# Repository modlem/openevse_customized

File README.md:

# openevse_customized
My own modified OpenEVSE

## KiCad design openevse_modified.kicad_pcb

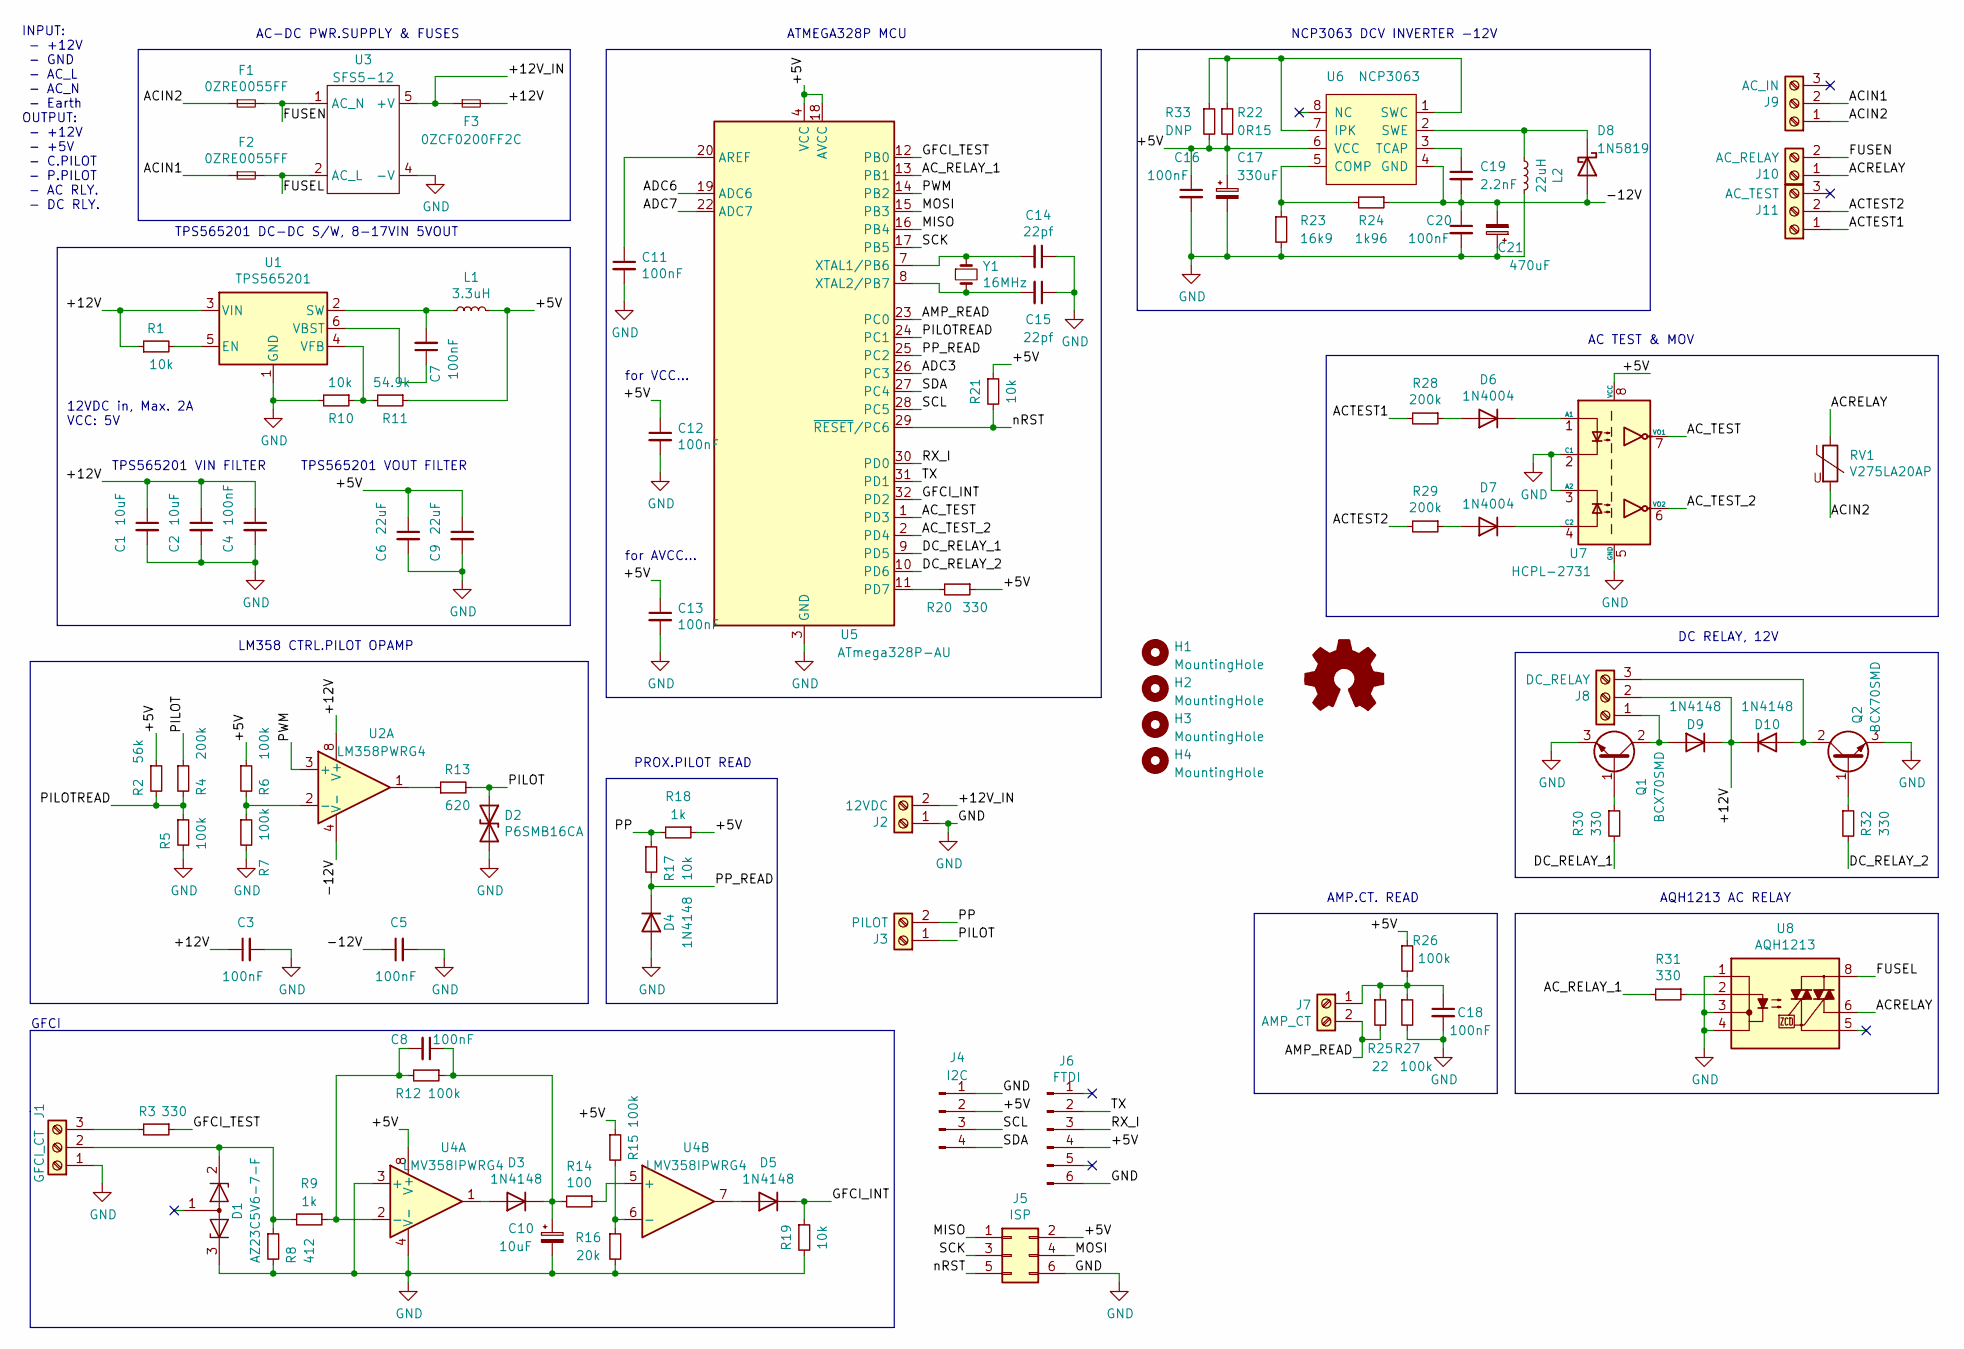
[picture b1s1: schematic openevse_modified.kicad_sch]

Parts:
C1, C2: 10uF; C_1210_3225Metric_Pad1.33x2.70mm_HandSolder
C3, C4, C5, C7, C8, C11, C12, C13, C16, C18, C20: 100nF; C_0805_2012Metric_Pad1.18x1.45mm_HandSolder
C6, C9: 22uF; C_0805_2012Metric_Pad1.18x1.45mm_HandSolder
C10: 10uF; CP_EIA-3216-18_Kemet-A_Pad1.58x1.35mm_HandSolder
C14, C15: 22pf; C_0805_2012Metric_Pad1.18x1.45mm_HandSolder
C17: 330uF; CP_Elec_8x10
C19: 2.2nF; C_0805_2012Metric_Pad1.18x1.45mm_HandSolder
C21: 470uF; CP_Radial_D12.5mm_P5.00mm
D1: AZ23C5V6-7-F; SOT-23
D2: P6SMB16CA; D_SMB_Handsoldering
D3, D4, D5, D9, D10: 1N4148; D_DO-35_SOD27_P7.62mm_Horizontal
D6, D7: 1N4004; D_DO-41_SOD81_P10.16mm_Horizontal
D8: 1N5819; D_SOD-123
F1, F2: 0ZRE0055FF; Fuse_BelFuse_0ZRE0055FF_L14.0mm_W4.1mm
F3: 0ZCF0200FF2C; Fuse_2920_7451Metric_Pad2.10x5.45mm_HandSolder
H1, H2, H3, H4: MountingHole; MountingHole_3.5mm
J1: GFCI_CT; JST_XH_B3B-XH-AM_1x03_P2.50mm_Vertical
J2: 12VDC; MC002075
J3: PILOT; MC002075
J4: I2C; JST_XH_B4B-XH-AM_1x04_P2.50mm_Vertical
J5: ISP; PinHeader_2x03_P2.54mm_Vertical
J6: FTDI; JST_XH_B6B-XH-AM_1x06_P2.50mm_Vertical
J7: AMP_CT; JST_XH_B2B-XH-AM_1x02_P2.50mm_Vertical
J8: DC_RELAY; MC002076
J9: AC_IN; MC002076
J10: AC_RELAY; MC002075
J11: AC_TEST; MC002076
L1: 3.3uH; L_TDK_VLP8040
L2: 22uH; L_Bourns_SRN6045TA
Q1, Q2: BCX70SMD; SOT-23_Handsoldering
R1, R10, R17, R19, R21: 10k; R_0805_2012Metric_Pad1.20x1.40mm_HandSolder
R2: 56k; R_0805_2012Metric_Pad1.20x1.40mm_HandSolder
R3, R20, R30, R31, R32: 330; R_0805_2012Metric_Pad1.20x1.40mm_HandSolder
R4: 200k; R_0805_2012Metric_Pad1.20x1.40mm_HandSolder
R5, R6, R7, R12, R15, R26, R27: 100k; R_0805_2012Metric_Pad1.20x1.40mm_HandSolder
R8: 412; R_0805_2012Metric_Pad1.20x1.40mm_HandSolder
R9, R18: 1k; R_0805_2012Metric_Pad1.20x1.40mm_HandSolder
R11: 54.9k; R_0805_2012Metric_Pad1.20x1.40mm_HandSolder
R13: 620; R_0805_2012Metric_Pad1.20x1.40mm_HandSolder
R14: 100; R_0805_2012Metric_Pad1.20x1.40mm_HandSolder
R16: 20k; R_0805_2012Metric_Pad1.20x1.40mm_HandSolder
R22: 0R15; R_0805_2012Metric_Pad1.20x1.40mm_HandSolder
R23: 16k9; R_0805_2012Metric_Pad1.20x1.40mm_HandSolder
R24: 1k96; R_0805_2012Metric_Pad1.20x1.40mm_HandSolder
R25: 22; R_0805_2012Metric_Pad1.20x1.40mm_HandSolder
R28, R29: 200k; R_Axial_DIN0207_L6.3mm_D2.5mm_P10.16mm_Horizontal
R33: DNP; R_1210_3225Metric_Pad1.30x2.65mm_HandSolder
RV1: V275LA20AP; RV_Disc_D15.5mm_W3.9mm_P7.5mm
U1: TPS565201; SOT-23-6
U2: LM358PWRG4; TSSOP-8_4.4x3mm_P0.65mm
U3: SFS5-12; Converter_ACDC_Recom_RAC20-xxDK_THT
U4: LMV358IPWRG4; TSSOP-8_4.4x3mm_P0.65mm
U5: ATmega328P-AU; TQFP-32_7x7mm_P0.8mm
U6: NCP3063; SOIC-8-1EP_3.9x4.9mm_P1.27mm_EP2.29x3mm
U7: HCPL-2731; DIP-8_W7.62mm_LongPads
U8: AQH1213; DIP-8_W7.62mm_LongPads
Y1: 16MHz; Crystal_SMD_HC49-SD_HandSoldering

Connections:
/+5V: C6.1, C9.1, C12.1, C13.1, C16.1, C17.1, J4.2, J5.2, J6.4, L1.2, R2.1, R6.1, R11.1, R15.1, R18.1, R20.1, R21.1, R22.2, R26.1, R33.2, U4.8 (V+), U5.4 (VCC), U5.6 (VCC), U5.18 (AVCC), U6.6 (VCC), U7.8 (VCC)
/+12V: C1.1, C2.1, C3.1, C4.1, D9.1 (K), D10.1 (K), F3.2, J8.2, R1.1, U1.3 (VIN), U2.8 (V+); also elsewhere on the board
/+12V_IN: F3.1, J2.2, U3.5 (+V); also elsewhere on the board
/-12V: C5.1, C19.2, C20.1, C21.2, D8.2 (A), R24.1, U2.4 (V-), U6.4 (GND)
/ACIN1: F2.1, J9.2; also elsewhere on the board
/ACIN2: F1.1, J9.1, RV1.2; also elsewhere on the board
/ACRELAY: J10.1, RV1.1, U8.6; also elsewhere on the board
/ACTEST1: J11.1, R28.2; also elsewhere on the board
/ACTEST2: J11.2, R29.2; also elsewhere on the board
/AC_RELAY_1: R31.2, U5.13 (PB1)
/AC_TEST: U5.1 (PD3), U7.7 (VO1)
/AC_TEST_2: U5.2 (PD4), U7.6 (VO2)
/ADC3: U5.26 (PC3)
/ADC6: U5.19 (ADC6)
/ADC7: U5.22 (ADC7)
/AMP_READ: J7.2, R25.2, U5.23 (PC0)
/DC_RELAY_1: R30.2, U5.9 (PD5)
/DC_RELAY_2: R32.2, U5.10 (PD6)
/FUSEL: F2.2, U3.2 (AC_L), U8.8
/FUSEN: F1.2, J10.2, U3.1 (AC_N); also elsewhere on the board
/GFCI_INT: D5.1 (K), R19.1, U5.32 (PD2)
/GFCI_TEST: R3.1, U5.12 (PB0)
/MISO: J5.1, U5.16 (PB4)
/MOSI: J5.4, U5.15 (PB3)
/PILOT: D2.1 (A1), J3.1, R4.1, R13.2; also elsewhere on the board
/PILOTREAD: R2.2, R4.2, R5.1, U5.24 (PC1)
/PP: J3.2, R17.1, R18.2; also elsewhere on the board
/PP_READ: D4.1 (K), R17.2, U5.25 (PC2)
/PWM: U2.3 (+), U5.14 (PB2)
/RX_I: J6.3, U5.30 (PD0)
/SCK: J5.3, U5.17 (PB5)
/SCL: J4.3, U5.28 (PC5)
/SDA: J4.4, U5.27 (PC4)
/TX: J6.2, U5.31 (PD1)
/nRST: J5.5, R21.2, U5.29 (~RESET/PC6)
GND: C1.2, C2.2, C3.2, C4.2, C5.2, C6.2, C9.2, C10.2, C11.2, C12.2, C13.2, C14.1, C15.1, C16.2, C17.2, C18.2, C20.2, C21.1, D1.3 (K), D2.2 (A2), D4.2 (A), J1.1, J2.1, J4.1, J5.6, J6.6, L2.2, Q1.3 (E), Q2.3 (E), R5.2, R7.2, R8.2, R10.2, R16.2, R19.2, R23.2, R27.2, U1.1 (GND), U3.4 (-V), U4.3 (+), U4.4 (V-), U5.3 (GND), U5.5 (GND), U5.21 (GND), U6.9, U7.2 (C1), U7.3 (A2), U7.5 (GND), U8.1, U8.3, U8.4; also elsewhere on the board
unnamed: C7.1, U1.6 (VBST)
unnamed: C7.2, L1.1, U1.2 (SW)
unnamed: C8.2, R9.1, R12.2, U4.2 (-)
unnamed: C8.1, C10.1, D3.1 (K), R12.1, R14.2
unnamed: C11.1, U5.20 (AREF)
unnamed: C14.2, U5.7 (XTAL1/PB6), Y1.1
unnamed: C15.2, U5.8 (XTAL2/PB7), Y1.2
unnamed: C18.1, J7.1, R25.1, R26.2, R27.1
unnamed: C19.1, U6.3 (TCAP)
unnamed: D1.2 (K), J1.2, R8.1, R9.2
unnamed: D3.2 (A), U4.1
unnamed: D5.2 (A), U4.7
unnamed: D6.1 (K), U7.1 (A1)
unnamed: D6.2 (A), R28.1
unnamed: D7.1 (K), U7.4 (C2)
unnamed: D7.2 (A), R29.1
unnamed: D8.1 (K), L2.1, U6.2 (SWE)
unnamed 53: D9.2 (A), J8.1, Q1.2 (C); also elsewhere on the board
unnamed 54: D10.2 (A), J8.3, Q2.2 (C); also elsewhere on the board
unnamed: J1.3, R3.2
unnamed: Q1.1 (B), R30.1
unnamed: Q2.1 (B), R32.1
unnamed: R1.2, U1.5 (EN)
unnamed: R6.2, R7.1, U2.2 (-)
unnamed: R10.1, R11.2, U1.4 (VFB)
unnamed: R13.1, U2.1
unnamed: R14.1, U4.5 (+)
unnamed: R15.2, R16.1, U4.6 (-)
unnamed: R20.2, U5.11 (PD7)
unnamed: R22.1, R33.1, U6.1 (SWC), U6.7 (IPK)
unnamed: R23.1, R24.2, U6.5 (COMP)
unnamed: R31.1, U8.2

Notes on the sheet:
ATMEGA328P MCU
INPUT: - +12V - GND - AC_L - AC_N - Earth OUTPUT: - +12V - +5V - C.PILOT - P.PILOT - AC RLY. - DC RLY.
AC TEST & MOV
12VDC in, Max. 2A VCC: 5V
DC RELAY, 12V
for AVCC...
for VCC...
AC-DC PWR.SUPPLY & FUSES
AQH1213 AC RELAY
AMP.CT. READ
NCP3063 DCV INVERTER -12V
TPS565201 VIN FILTER
PROX.PILOT READ
LM358 CTRL.PILOT OPAMP
TPS565201 VOUT FILTER
TPS565201 DC-DC S/W, 8-17VIN 5VOUT
GFCI

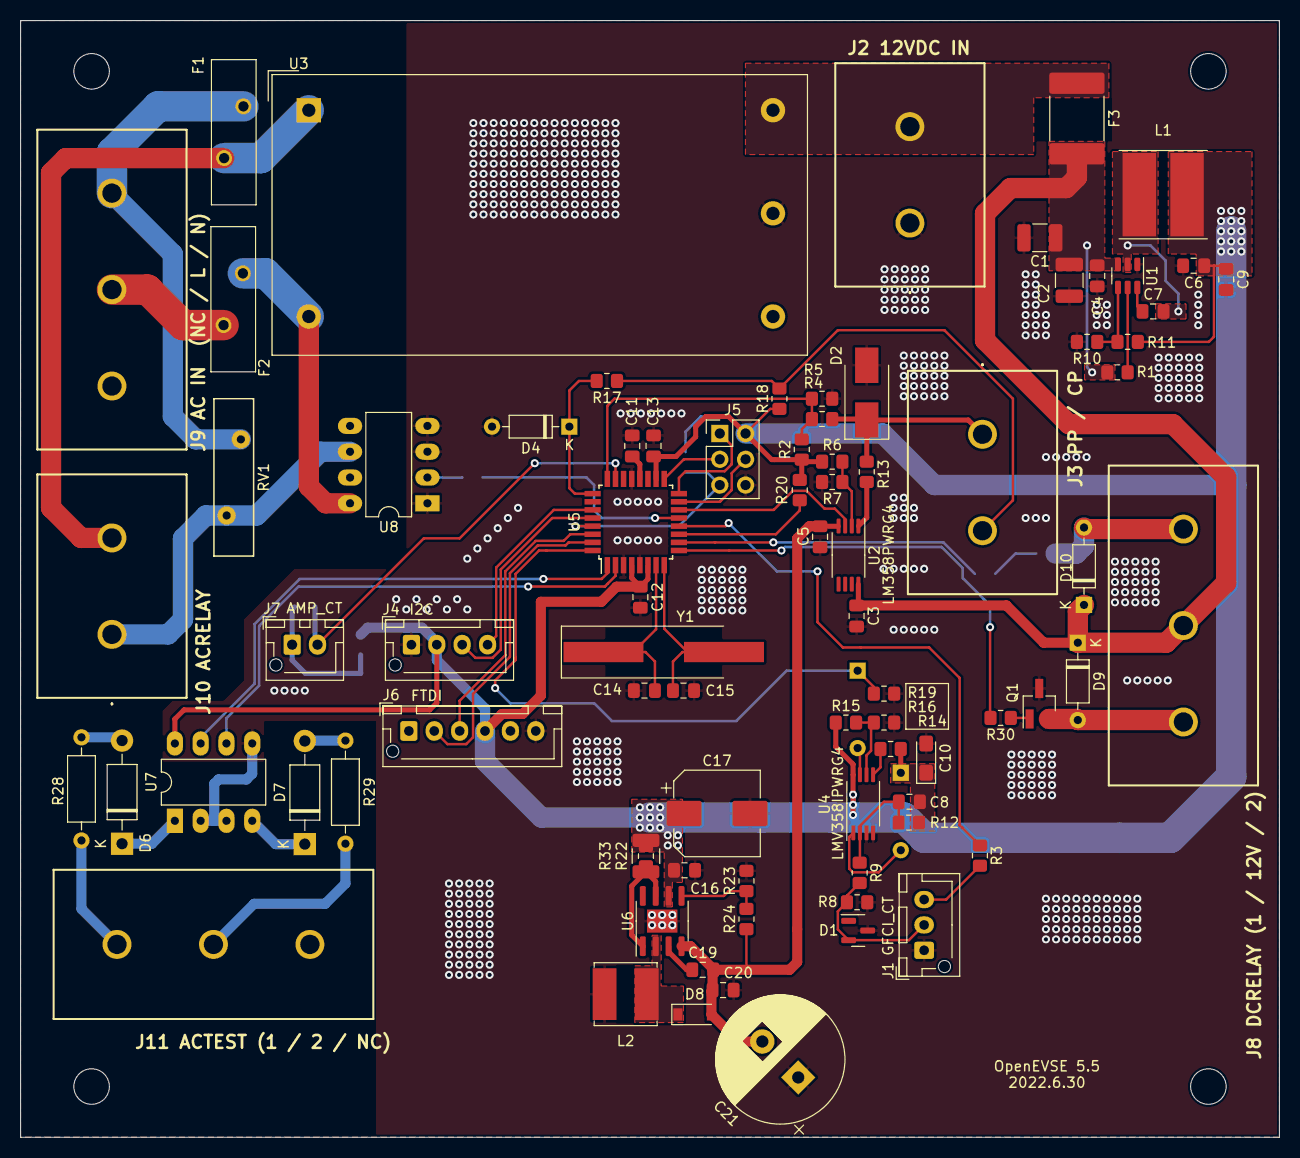
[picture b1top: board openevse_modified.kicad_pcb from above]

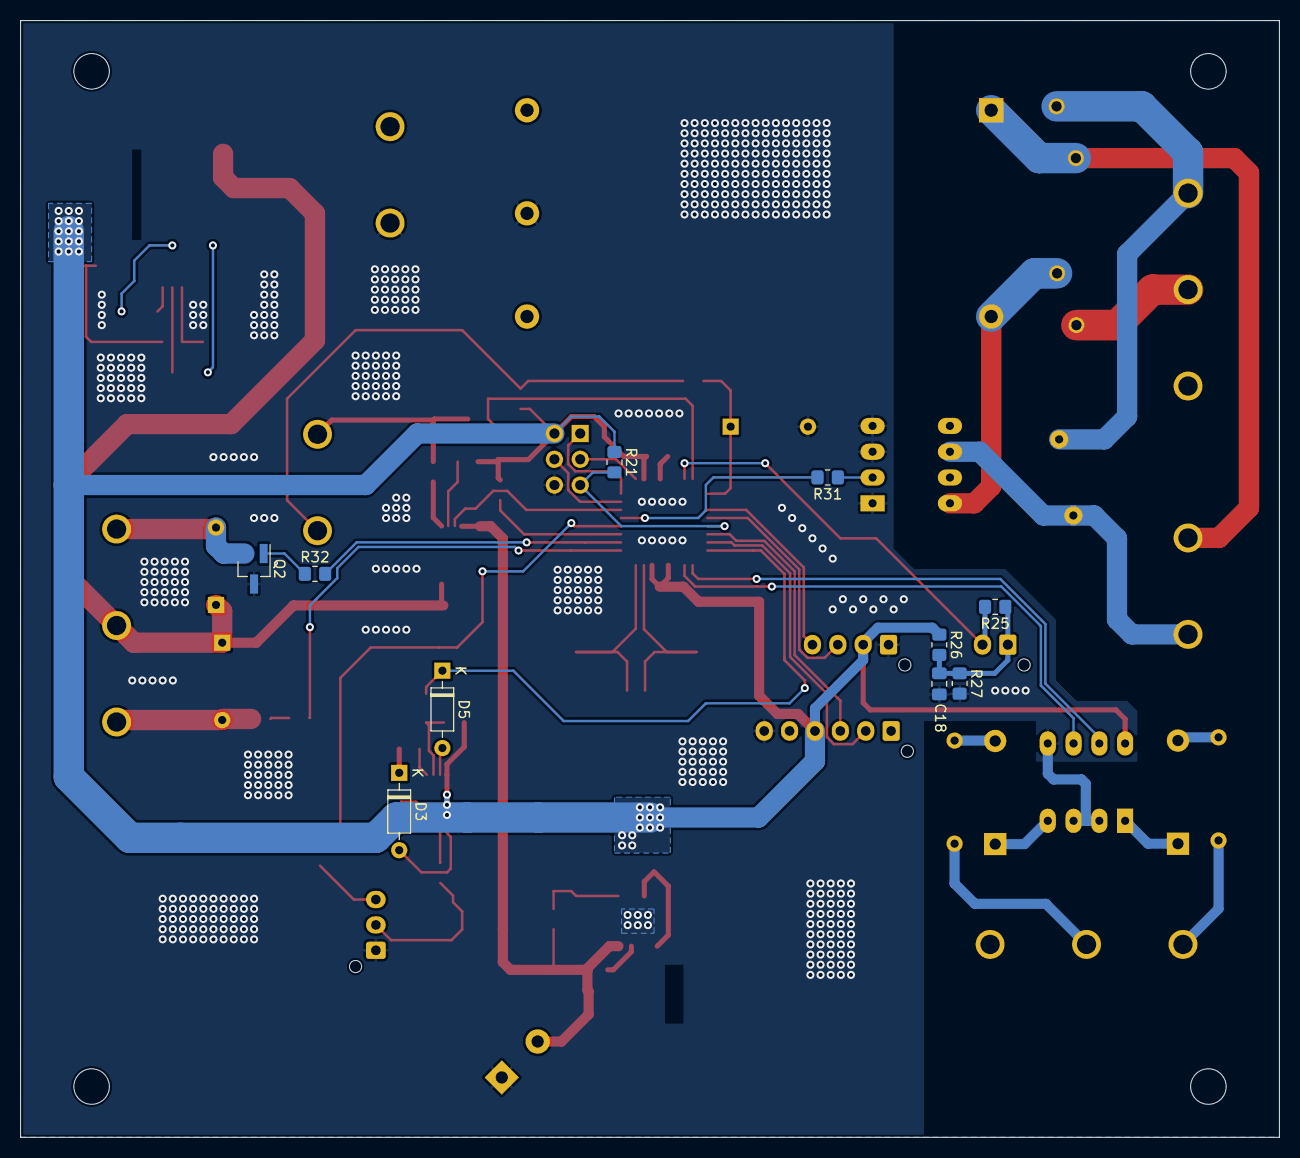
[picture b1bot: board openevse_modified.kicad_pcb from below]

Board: 2 copper layers, 124.0 x 110.0 mm, 96 parts (10 on the bottom side), 65 nets.

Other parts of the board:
J2 12VDC IN: 12VDC; MC002075
J3 PP / CP: PILOT; MC002075
J8 DCRELAY (1 / 12V / 2): DC_RELAY; MC002076
J9 AC IN  (NC / L / N): AC_IN; MC002076
J10 ACRELAY: AC_RELAY; MC002075
J11 ACTEST (1 / 2 / NC): AC_TEST; MC002076

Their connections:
/+12V: J8 DCRELAY (1 / 12V / 2).2; also elsewhere on the board
/+12V_IN: J2 12VDC IN.2; also elsewhere on the board
/ACIN1: J9 AC IN (NC / L / N).2; also elsewhere on the board
/ACIN2: J9 AC IN (NC / L / N).1; also elsewhere on the board
/ACRELAY: J10 ACRELAY.1; also elsewhere on the board
/ACTEST1: J11 ACTEST (1 / 2 / NC).1; also elsewhere on the board
/ACTEST2: J11 ACTEST (1 / 2 / NC).2; also elsewhere on the board
/FUSEN: J10 ACRELAY.2; also elsewhere on the board
/PILOT: J3 PP / CP.1; also elsewhere on the board
/PP: J3 PP / CP.2; also elsewhere on the board
GND: J2 12VDC IN.1; also elsewhere on the board
unnamed 53: J8 DCRELAY (1 / 12V / 2).1; also elsewhere on the board
unnamed 54: J8 DCRELAY (1 / 12V / 2).3; also elsewhere on the board

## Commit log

2022-06-22 OpenEVSE modified ver1
    openevse_modified_190729_0451.7z
2022-06-30 Gerber generated
